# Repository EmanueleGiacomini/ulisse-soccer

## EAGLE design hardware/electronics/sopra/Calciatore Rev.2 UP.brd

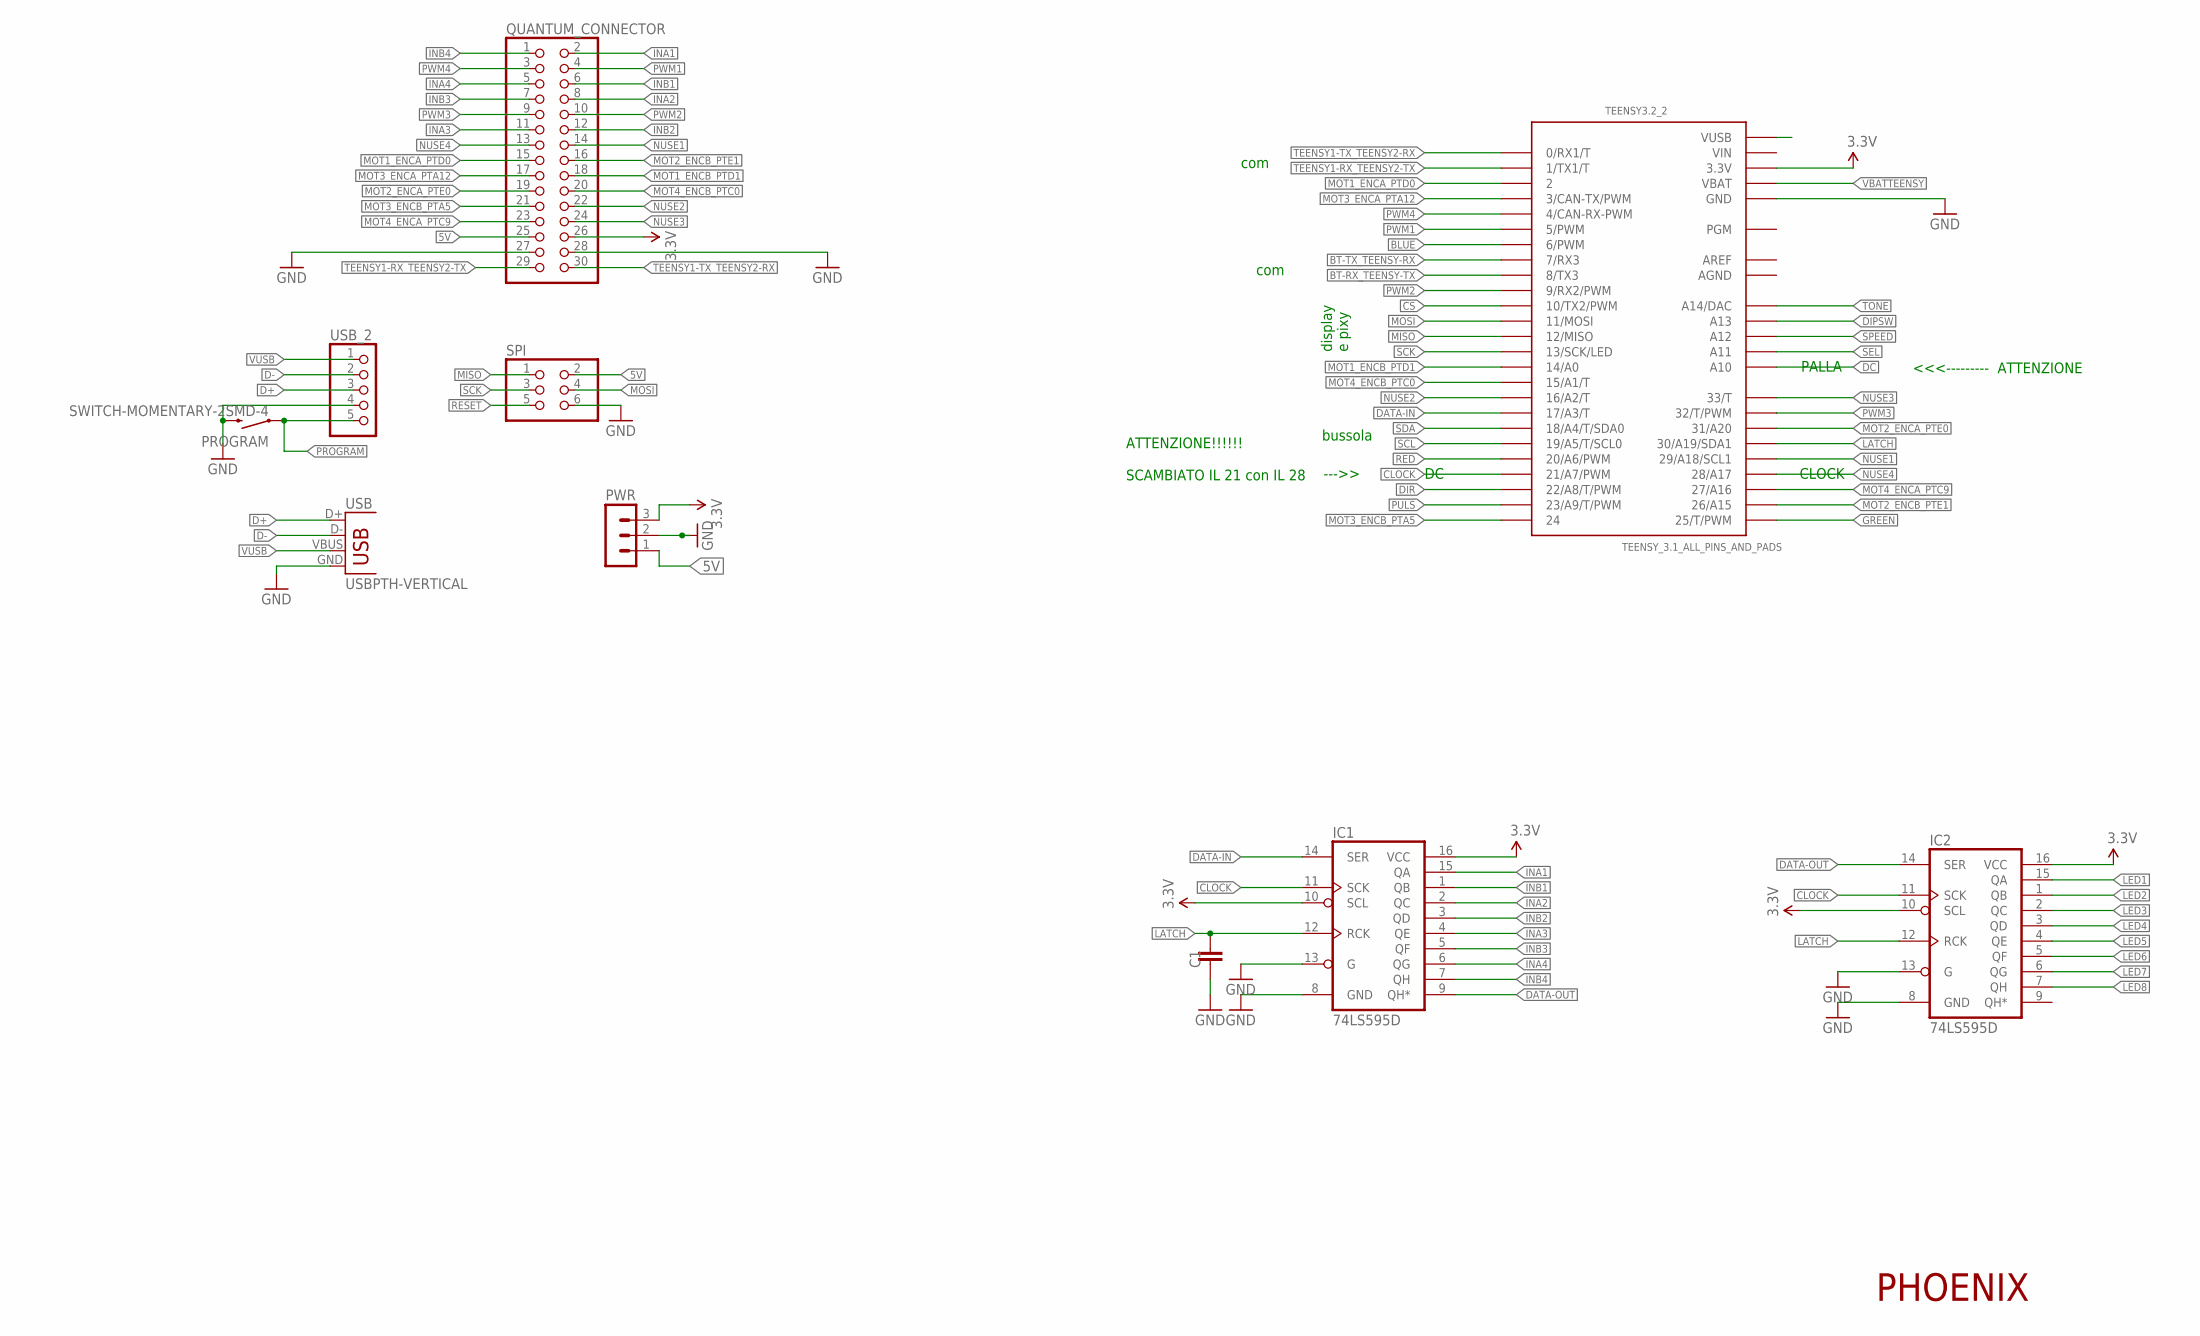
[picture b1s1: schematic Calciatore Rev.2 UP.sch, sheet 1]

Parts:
C1: C-EUC1206; C1206
IC1, IC2: 74LS595D; SO16
PROGRAM: SWITCH-MOMENTARY-2SMD-4; TACTILE_SWITCH_TALL
PWR: MA03-1
QUANTUM_CONNECTOR: PINHD-2X15; 2X15
SPI: PINHD-2X3; 2X03
TEENSY3.2_2: TEENSY_3.1_ALL_PINS_AND_PADS; TEENSY3_ALL_PINS_&_PADS
USB: USBPTH-VERTICAL; USB-B-PTH-VERTICAL
USB_2: PINHD-1X5; 1X05

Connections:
3.3V: IC1.10 (SCL), IC1.16 (VCC), IC2.10 (SCL), IC2.16 (VCC), PWR.3, QUANTUM_CONNECTOR.26, TEENSY3.2_2.3.3V, TEENSY3.2_2.3.3V1 (3.3V), TEENSY3.2_2.3.3V2 (3.3V); also elsewhere on the board
5V: PWR.1, QUANTUM_CONNECTOR.25, SPI.2; also elsewhere on the board
AGND: TEENSY3.2_2.AGND
AREF: TEENSY3.2_2.AREF
BLUE: TEENSY3.2_2.6 (6/PWM); also elsewhere on the board
BT-RX_TEENSY-TX: TEENSY3.2_2.8 (8/TX3); also elsewhere on the board
BT-TX_TEENSY-RX: TEENSY3.2_2.7 (7/RX3); also elsewhere on the board
CLOCK: IC1.11 (SCK), IC2.11 (SCK), TEENSY3.2_2.21/A7 (21/A7/PWM)
CS: TEENSY3.2_2.10 (10/TX2/PWM); also elsewhere on the board
D+: USB.D+, USB_2.3
D-: USB.D-, USB_2.2
DATA-IN: IC1.14 (SER), TEENSY3.2_2.17/A3 (17/A3/T)
DATA-OUT: IC1.9 (QH*), IC2.14 (SER)
DC: TEENSY3.2_2.A10; also elsewhere on the board
DIPSW: TEENSY3.2_2.A13; also elsewhere on the board
DIR: TEENSY3.2_2.22/A8 (22/A8/T/PWM); also elsewhere on the board
GND: C1.1, IC1.8 (GND), IC1.13 (G), IC2.8 (GND), IC2.13 (G), PROGRAM.B2 (2), PWR.2, QUANTUM_CONNECTOR.27, QUANTUM_CONNECTOR.28, SPI.6, TEENSY3.2_2.GND, TEENSY3.2_2.GND1 (GND), TEENSY3.2_2.GND2 (GND), USB.GND, USB_2.4; also elsewhere on the board
GREEN: TEENSY3.2_2.25 (25/T/PWM); also elsewhere on the board
INA1: IC1.15 (QA), QUANTUM_CONNECTOR.2
INA2: IC1.2 (QC), QUANTUM_CONNECTOR.8
INA3: IC1.4 (QE), QUANTUM_CONNECTOR.11
INA4: IC1.6 (QG), QUANTUM_CONNECTOR.5
INB1: IC1.1 (QB), QUANTUM_CONNECTOR.6
INB2: IC1.3 (QD), QUANTUM_CONNECTOR.12
INB3: IC1.5 (QF), QUANTUM_CONNECTOR.7
INB4: IC1.7 (QH), QUANTUM_CONNECTOR.1
LATCH: C1.2, IC1.12 (RCK), IC2.12 (RCK), TEENSY3.2_2.30 (30/A19/SDA1)
LED1: IC2.15 (QA); also elsewhere on the board
LED2: IC2.1 (QB); also elsewhere on the board
LED3: IC2.2 (QC); also elsewhere on the board
LED4: IC2.3 (QD); also elsewhere on the board
LED5: IC2.4 (QE); also elsewhere on the board
LED6: IC2.5 (QF); also elsewhere on the board
LED7: IC2.6 (QG); also elsewhere on the board
LED8: IC2.7 (QH); also elsewhere on the board
MISO: SPI.1, TEENSY3.2_2.12 (12/MISO)
MOSI: SPI.4, TEENSY3.2_2.11 (11/MOSI); also elsewhere on the board
MOT1_ENCA_PTD0: QUANTUM_CONNECTOR.15, TEENSY3.2_2.2
MOT1_ENCB_PTD1: QUANTUM_CONNECTOR.18, TEENSY3.2_2.14/A0
MOT2_ENCA_PTE0: QUANTUM_CONNECTOR.19, TEENSY3.2_2.31 (31/A20)
MOT2_ENCB_PTE1: QUANTUM_CONNECTOR.16, TEENSY3.2_2.26 (26/A15)
MOT3_ENCA_PTA12: QUANTUM_CONNECTOR.17, TEENSY3.2_2.3 (3/CAN-TX/PWM)
MOT3_ENCB_PTA5: QUANTUM_CONNECTOR.21, TEENSY3.2_2.24
MOT4_ENCA_PTC9: QUANTUM_CONNECTOR.23, TEENSY3.2_2.27 (27/A16)
MOT4_ENCB_PTC0: QUANTUM_CONNECTOR.20, TEENSY3.2_2.15/A1 (15/A1/T)
NUSE1: QUANTUM_CONNECTOR.14, TEENSY3.2_2.29 (29/A18/SCL1)
NUSE2: QUANTUM_CONNECTOR.22, TEENSY3.2_2.16/A2 (16/A2/T)
NUSE3: QUANTUM_CONNECTOR.24, TEENSY3.2_2.33 (33/T)
NUSE4: QUANTUM_CONNECTOR.13, TEENSY3.2_2.28 (28/A17)
PROGRAM: PROGRAM.A2 (1), USB_2.5
PULS: TEENSY3.2_2.23/A9 (23/A9/T/PWM); also elsewhere on the board
PWM1: QUANTUM_CONNECTOR.4, TEENSY3.2_2.5 (5/PWM)
PWM2: QUANTUM_CONNECTOR.10, TEENSY3.2_2.9 (9/RX2/PWM)
PWM3: QUANTUM_CONNECTOR.9, TEENSY3.2_2.32 (32/T/PWM)
PWM4: QUANTUM_CONNECTOR.3, TEENSY3.2_2.4 (4/CAN-RX-PWM)
RED: TEENSY3.2_2.20/A6 (20/A6/PWM); also elsewhere on the board
RESET: SPI.5
SCK: SPI.3, TEENSY3.2_2.13 (13/SCK/LED); also elsewhere on the board
SCL: TEENSY3.2_2.19/A5 (19/A5/T/SCL0); also elsewhere on the board
SDA: TEENSY3.2_2.18/A4 (18/A4/T/SDA0); also elsewhere on the board
SEL: TEENSY3.2_2.A11; also elsewhere on the board
SPEED: TEENSY3.2_2.A12; also elsewhere on the board
TEENSY1-RX_TEENSY2-TX: QUANTUM_CONNECTOR.29, TEENSY3.2_2.1 (1/TX1/T)
TEENSY1-TX_TEENSY2-RX: QUANTUM_CONNECTOR.30, TEENSY3.2_2.0 (0/RX1/T)
TONE: TEENSY3.2_2.RESET/DAC (A14/DAC); also elsewhere on the board
VBATTEENSY: TEENSY3.2_2.VBAT
VIN: TEENSY3.2_2.VIN
VUSB: USB.VBUS, USB_2.1

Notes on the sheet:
PHOENIX
display e pixy
bussola
com
ATTENZIONE!!!!!! SCAMBIATO IL 21 con IL 28
--->>
<<<--------- ATTENZIONE
CLOCK
PALLA

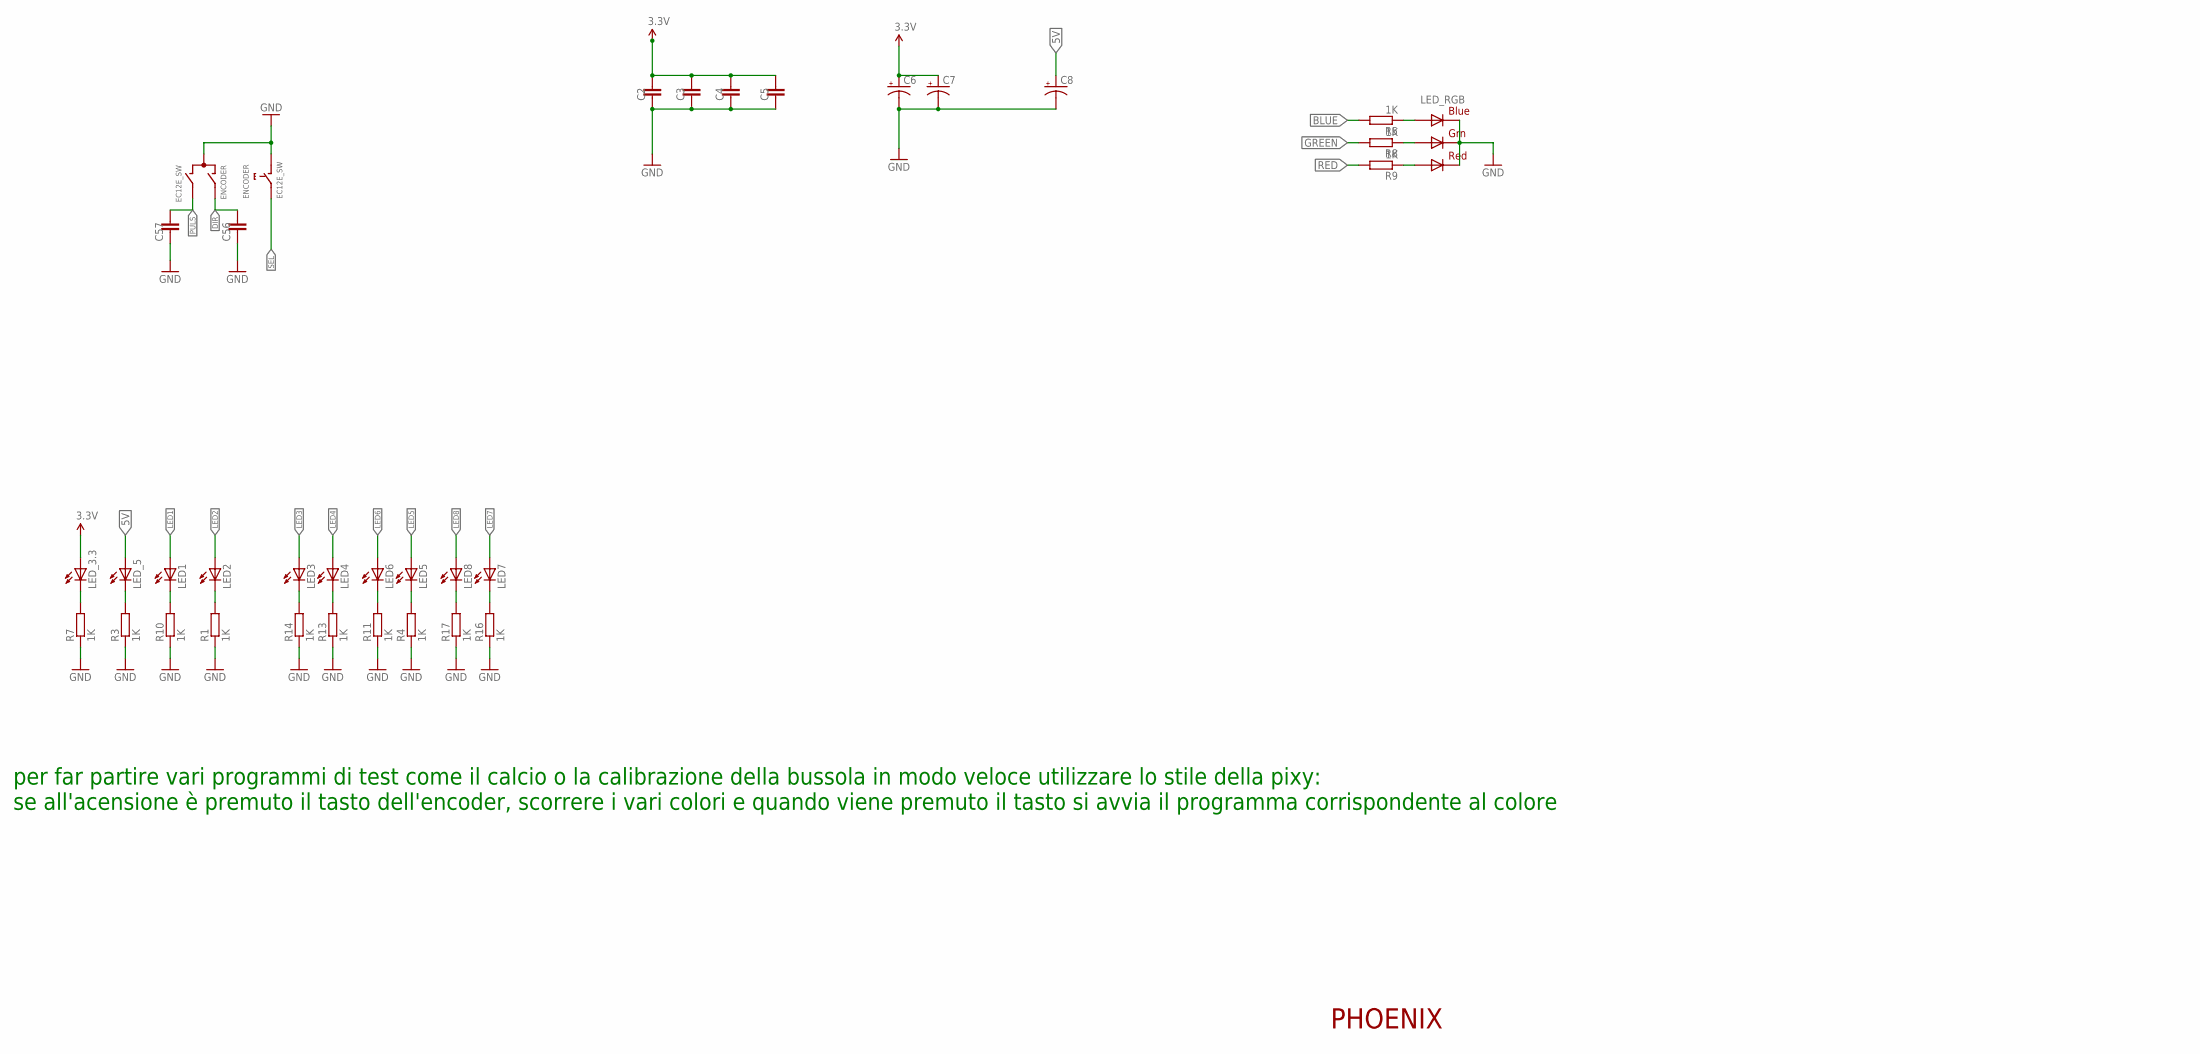
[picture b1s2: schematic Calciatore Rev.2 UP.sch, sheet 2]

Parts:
C2, C3, C4, C5, C56, C57: C-EUC1206; C1206
C6, C7, C8: CPOL-USE3.5-8; E3,5-8
ENCODER: EC12E_SW; ALPS_EC12E_SW
LED1, LED2, LED3, LED4, LED5, LED6, LED7, LED8: LEDSMT1206; 1206
LED_3.3, LED_5: LEDSMT1206; 1206
LED_RGB: RGBLED5050
R1, R3, R4, R5, R7, R8, R9, R10, R11, R13, R14, R16, R17: 1K; M1206

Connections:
3.3V: C2.2, C3.2, C4.2, C5.2, C6.+, C7.+, LED_3.3.A; also elsewhere on the board
5V: C8.+, LED_5.A; also elsewhere on the board
BLUE: R5.2; also elsewhere on the board
DIR: C56.2, ENCODER.A; also elsewhere on the board
GND: C2.1, C3.1, C4.1, C5.1, C6.-, C7.-, C8.-, C56.1, C57.1, ENCODER.C, ENCODER.D (1), LED_RGB.4 (BLUE_C), LED_RGB.5 (RED_C), LED_RGB.6 (GREEN_C), R1.1, R3.1, R4.1, R7.1, R10.1, R11.1, R13.1, R14.1, R16.1, R17.1; also elsewhere on the board
GREEN: R8.2; also elsewhere on the board
LED1: LED1.A; also elsewhere on the board
LED2: LED2.A; also elsewhere on the board
LED3: LED3.A; also elsewhere on the board
LED4: LED4.A; also elsewhere on the board
LED5: LED5.A; also elsewhere on the board
LED6: LED6.A; also elsewhere on the board
LED7: LED7.A; also elsewhere on the board
LED8: LED8.A; also elsewhere on the board
LED_3.3: LED_3.3.C, R7.2
unnamed: LED2.C, R1.2
unnamed: LED_5.C, R3.2
unnamed: LED5.C, R4.2
unnamed: LED6.C, R11.2
unnamed: LED7.C, R16.2
unnamed: LED_RGB.3 (BLUE_A), R5.1
unnamed: LED_RGB.1 (GREEN_A), R8.1
unnamed: LED_RGB.2 (RED_A), R9.1
unnamed: LED1.C, R10.2
unnamed: LED4.C, R13.2
unnamed: LED3.C, R14.2
unnamed: LED8.C, R17.2
PULS: C57.2, ENCODER.B; also elsewhere on the board
RED: R9.2; also elsewhere on the board
SEL: ENCODER.E (2); also elsewhere on the board

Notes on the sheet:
PHOENIX
per far partire vari programmi di test come il calcio o la calibrazione della bussola in modo veloce utilizzare lo stile della pixy: se all'acensione è premuto il tasto dell'encoder, scorrere i vari colori e quando viene premuto il tasto si avvia il programma corrispondente al colore

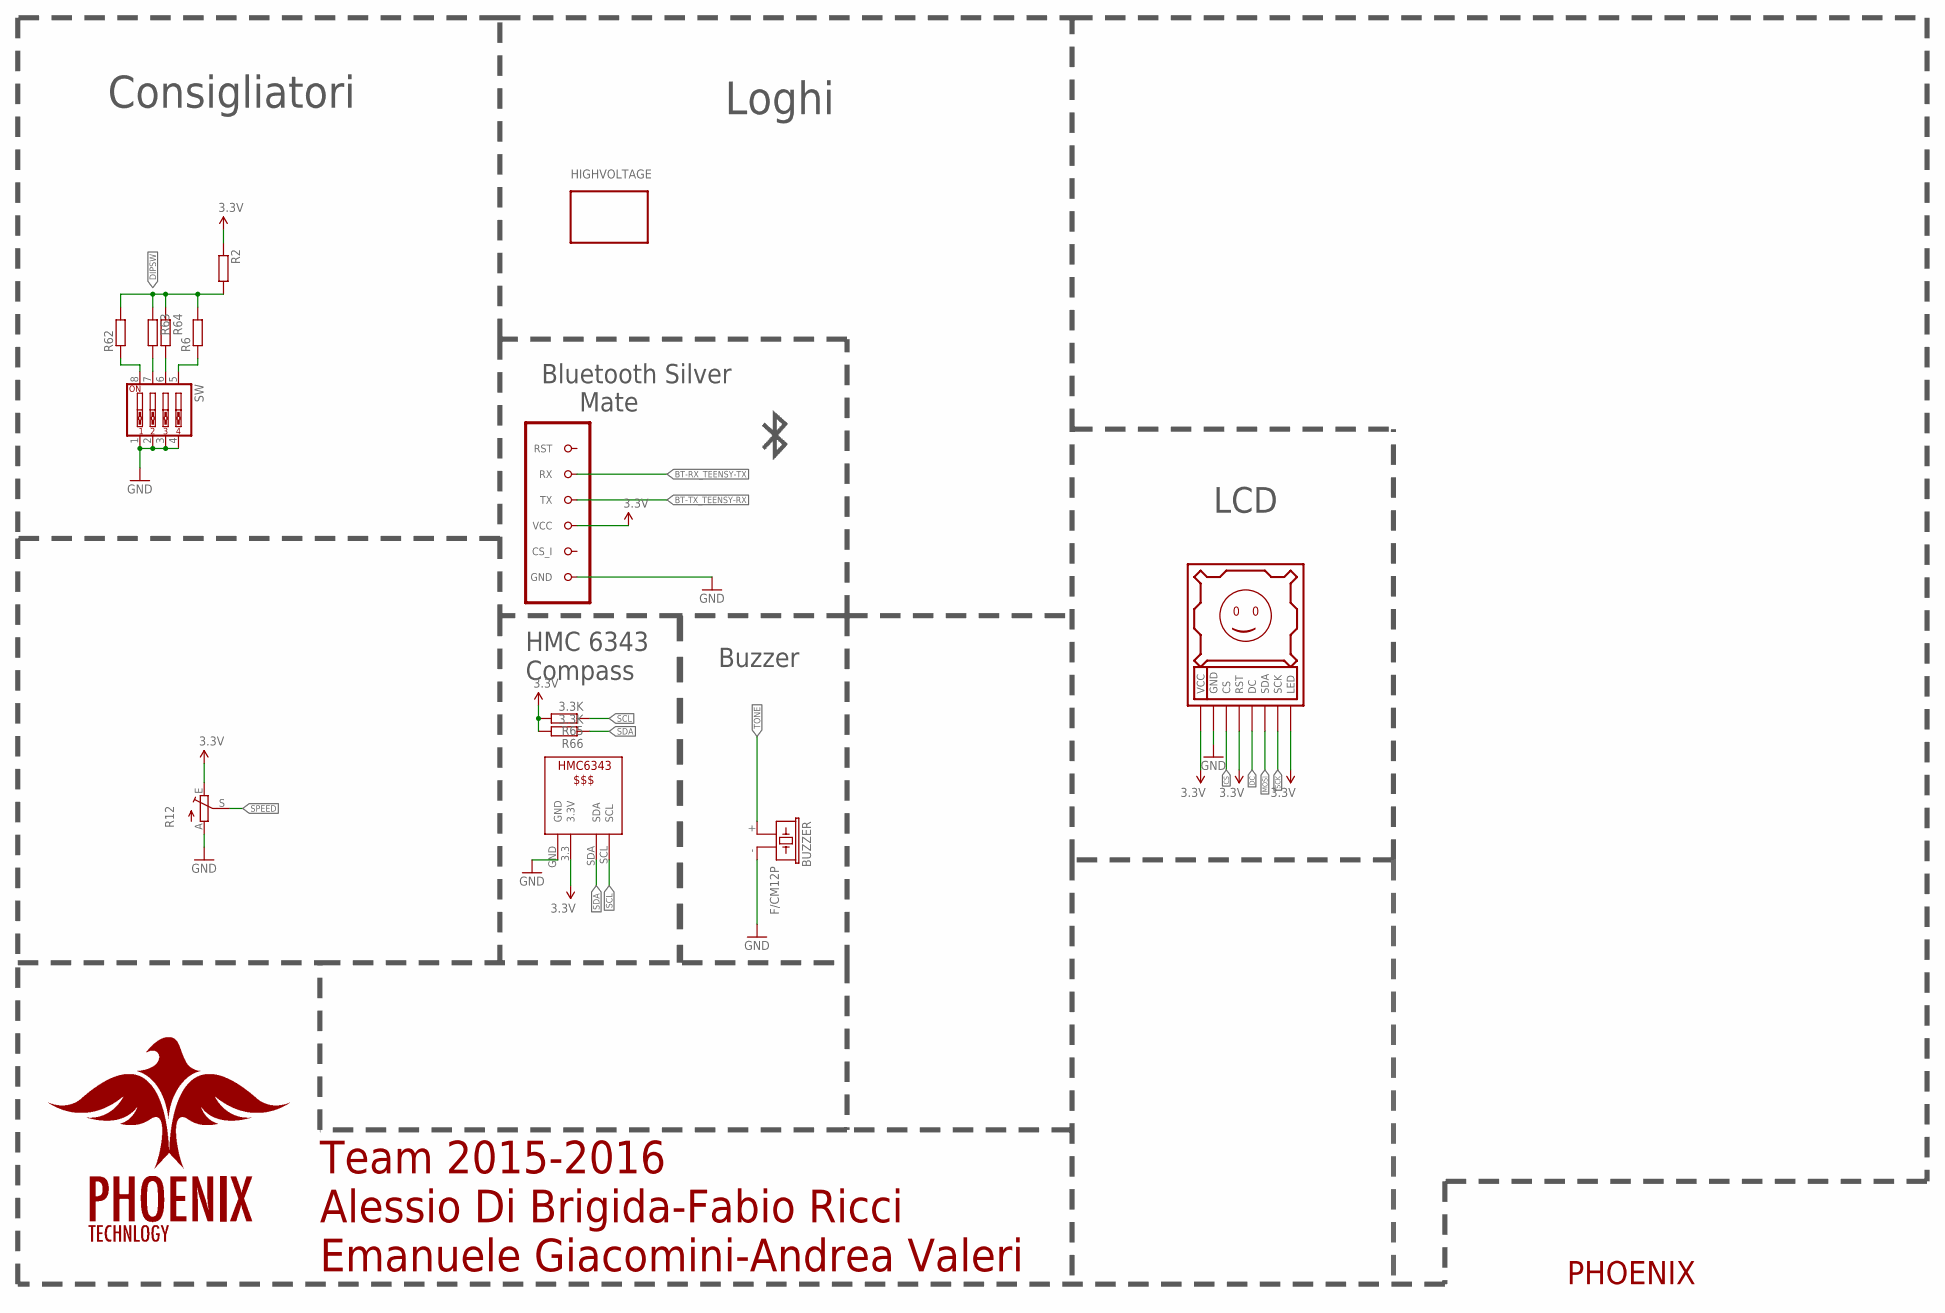
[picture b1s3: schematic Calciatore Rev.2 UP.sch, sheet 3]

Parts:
BUZZER: F/CM12P
DISPLAY1: DISPLAY128X128
HIGHVOLTAGE: LOGO; LOGOHV
R2, R6, R62, R63, R64: 10K; M1206
R12: TRIM_EU-S63P; S63P
R65, R66: 3.3K; M1206
SW: SW_DIP-4; EDG-04
U$5: HMC6343
U$9: BLUETOOTH

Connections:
3.3V: DISPLAY1.LED, DISPLAY1.RST, DISPLAY1.VCC, R2.1, R12.E, R65.2, R66.2, U$5.3.3 (3.3V), U$9.VCC; also elsewhere on the board
BT-RX_TEENSY-TX: U$9.RX; also elsewhere on the board
BT-TX_TEENSY-RX: U$9.TX; also elsewhere on the board
CS: DISPLAY1.CS; also elsewhere on the board
DC: DISPLAY1.DC; also elsewhere on the board
DIPSW: R2.2, R6.2, R62.2, R63.1, R64.1; also elsewhere on the board
GND: BUZZER.- (2), DISPLAY1.GND, R12.A, SW.1, SW.2, SW.3, SW.4, U$5.GND, U$9.GND; also elsewhere on the board
MOSI: DISPLAY1.SDA; also elsewhere on the board
unnamed: R64.2, SW.6
unnamed: R62.1, SW.8
unnamed: R6.1, SW.5
unnamed: R63.2, SW.7
SCK: DISPLAY1.SCK; also elsewhere on the board
SCL: R65.1, U$5.SCL; also elsewhere on the board
SDA: R66.1, U$5.SDA; also elsewhere on the board
SPEED: R12.S; also elsewhere on the board
TONE: BUZZER.+ (1); also elsewhere on the board

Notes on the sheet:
LCD
Buzzer
Bluetooth Silver Mate
HMC 6343 Compass
Consigliatori
Loghi
Team 2015-2016 Alessio Di Brigida-Fabio Ricci Emanuele Giacomini-Andrea Valeri
PHOENIX

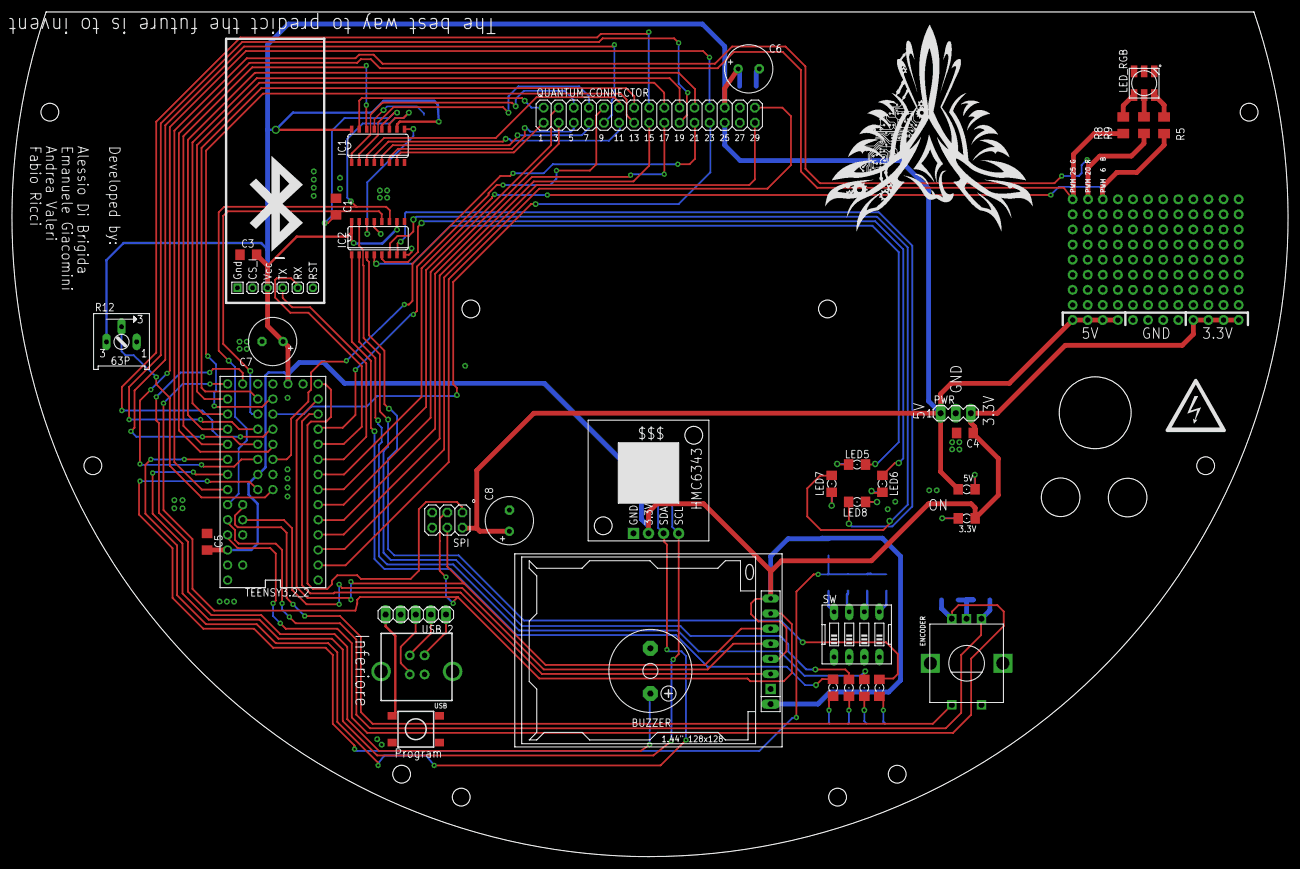
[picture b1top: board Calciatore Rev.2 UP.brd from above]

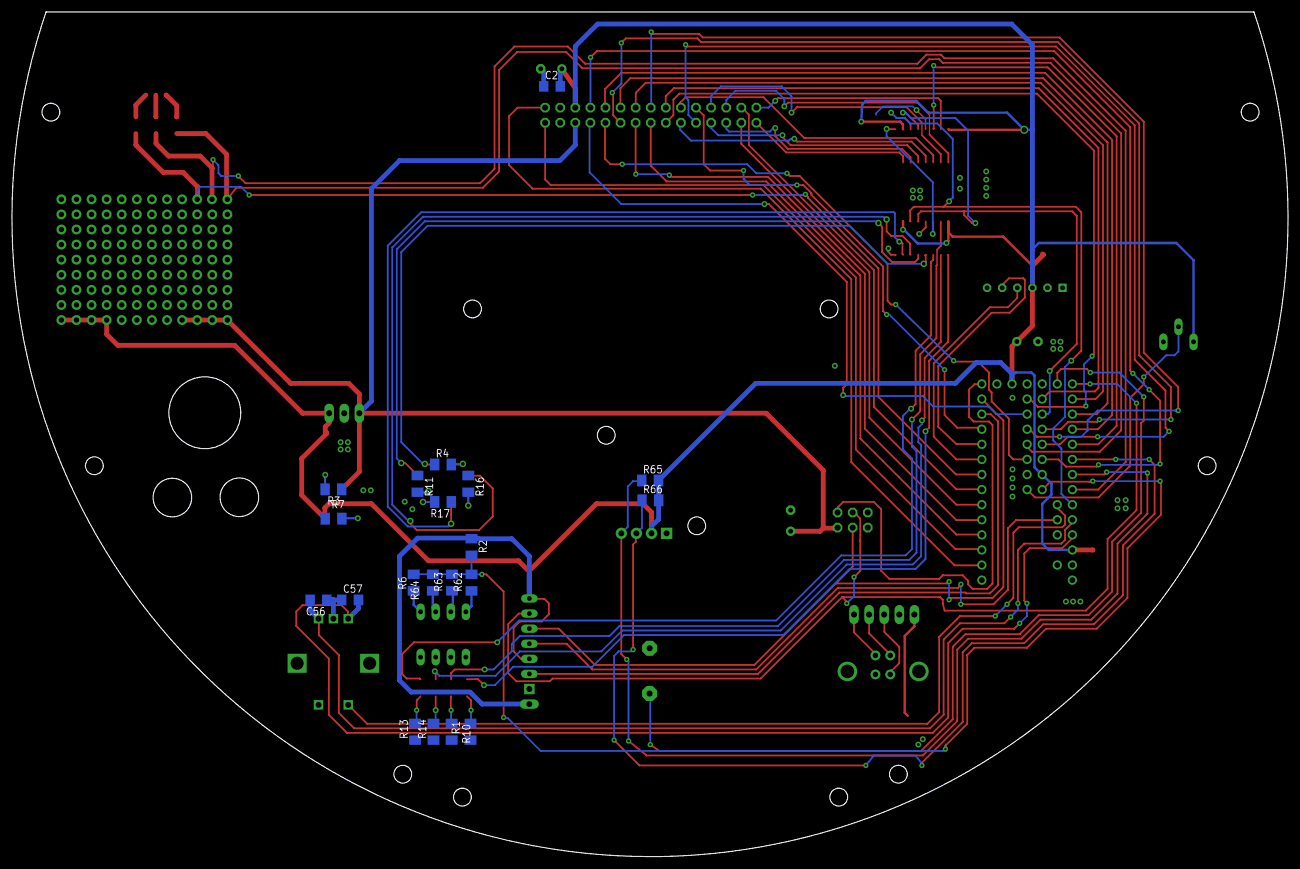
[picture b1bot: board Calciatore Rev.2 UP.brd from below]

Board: 2 copper layers, 214.8 x 142.2 mm, 59 parts (20 on the bottom side), 80 nets.

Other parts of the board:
U$1: PHOENIX

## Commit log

2018-04-19 Add Makefile, teensy stuff
2018-04-22 Add hardware schematic and board. Various updates on libraries
2018-04-23 Updated source files
2018-04-28 Added controller input reader (basic) =)
2018-05-05 Modified way too much stuff :)
2018-05-07 Add packet_handler and some minor stuff
2018-06-19 Slightly mod of packet_handler
2018-06-21 Finished packet_handler, started ulisse_client
2018-06-27 Various changes to host and ulisse_client
2018-06-27 more updates :)
2018-06-27 Building host
2018-07-12 Add makefile.linux, c-utilities, started teensy libs
2018-07-30 Updated makefiles
2018-07-31 More updates for teensy makefile
    Also added robocar py file for backup
2018-08-02 Added an hopefully working makefile
2018-08-27 Solved makefile issues
    Program wont somehow start on the teensy
2018-08-28 Makefile finally works
    Now heading to important stuff
2018-08-29 Completed DigIO and pins libraries
2018-08-30 Completed eeprom lib (Need to test)
2018-08-30 Added uart.c updated makefile.teensy
2018-09-04 Add systime_init and usb_init func

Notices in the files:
parts and their libraries:
SparkFun-DigitalIC: Licensing: Creative Commons ShareAlike 4.0 International - https://creativecommons.org/licenses/by-sa/4.0
